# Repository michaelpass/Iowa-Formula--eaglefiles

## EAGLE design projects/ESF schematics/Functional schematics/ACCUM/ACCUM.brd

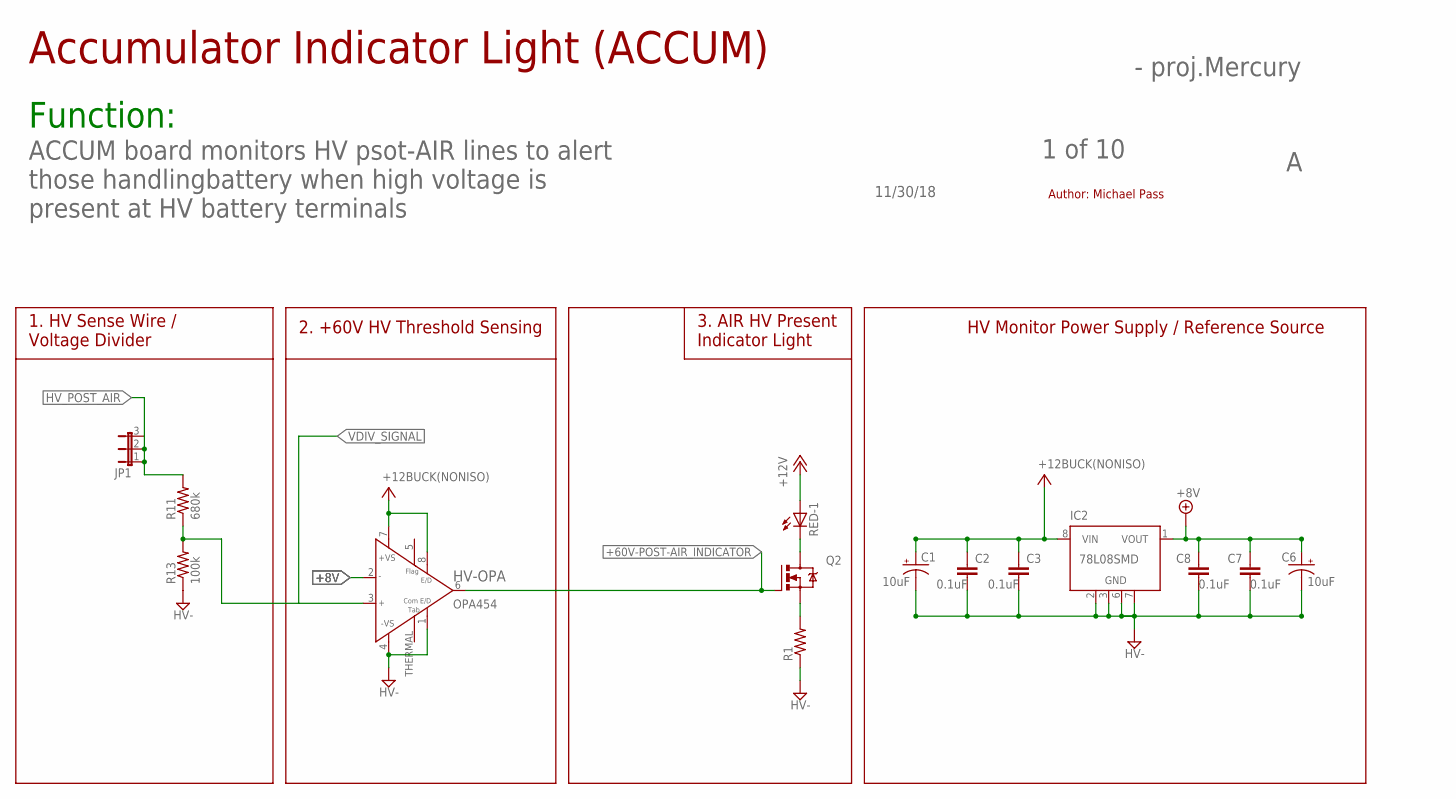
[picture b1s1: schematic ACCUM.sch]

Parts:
C1, C6: 10uF; 085CS_1AW
C2, C3, C7, C8: 0.1uF; C0805
HV-OPA: OPA454; SO08GP
IC2: 78L08SMD; SO08
JP1: JP2W
Q2: IRLZ44Z; TO220BH
R1: R-US_R0805; R0805
R11: 680k; R0805
R13: 100k; R0805
RED: LZR184

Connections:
+8V: C6.+, C7.1, C8.1, HV-OPA.2 (IN-), IC2.1 (VOUT)
+12V: RED.A1 (A)
+60V-POST-AIR_INDICATOR: HV-OPA.6 (OUT), Q2.G
GND: R1.1, R13.1
HV-: C1.-, C2.2, C3.2, C6.-, C7.2, C8.2, HV-OPA.1 (E/DCOM), HV-OPA.4 (-VS), IC2.2 (GND), IC2.3 (GND), IC2.6 (GND), IC2.7 (GND)
HV_POST_AIR: JP1.1, JP1.2, JP1.3, R11.2
unnamed: Q2.D, RED.K1 (C)
unnamed: Q2.S, R1.2
V+: C1.+, C2.1, C3.1, HV-OPA.7 (+VS), HV-OPA.8 (E/D), IC2.8 (VIN)
VDIV_SIGNAL: HV-OPA.3 (IN+), R11.1, R13.2

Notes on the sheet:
2. +60V HV Threshold Sensing
1. HV Sense Wire / Voltage Divider
HV Monitor Power Supply / Reference Source
3. AIR HV Present Indicator Light
Accumulator Indicator Light (ACCUM)
Function:
11/30/18
1 of 10
- proj.Mercury
ACCUM board monitors HV psot-AIR lines to alert those handlingbattery when high voltage is present at HV battery terminals
Author: Michael Pass

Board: 2 copper layers, 14 parts (0 on the bottom side), 9 nets, no tracks yet.

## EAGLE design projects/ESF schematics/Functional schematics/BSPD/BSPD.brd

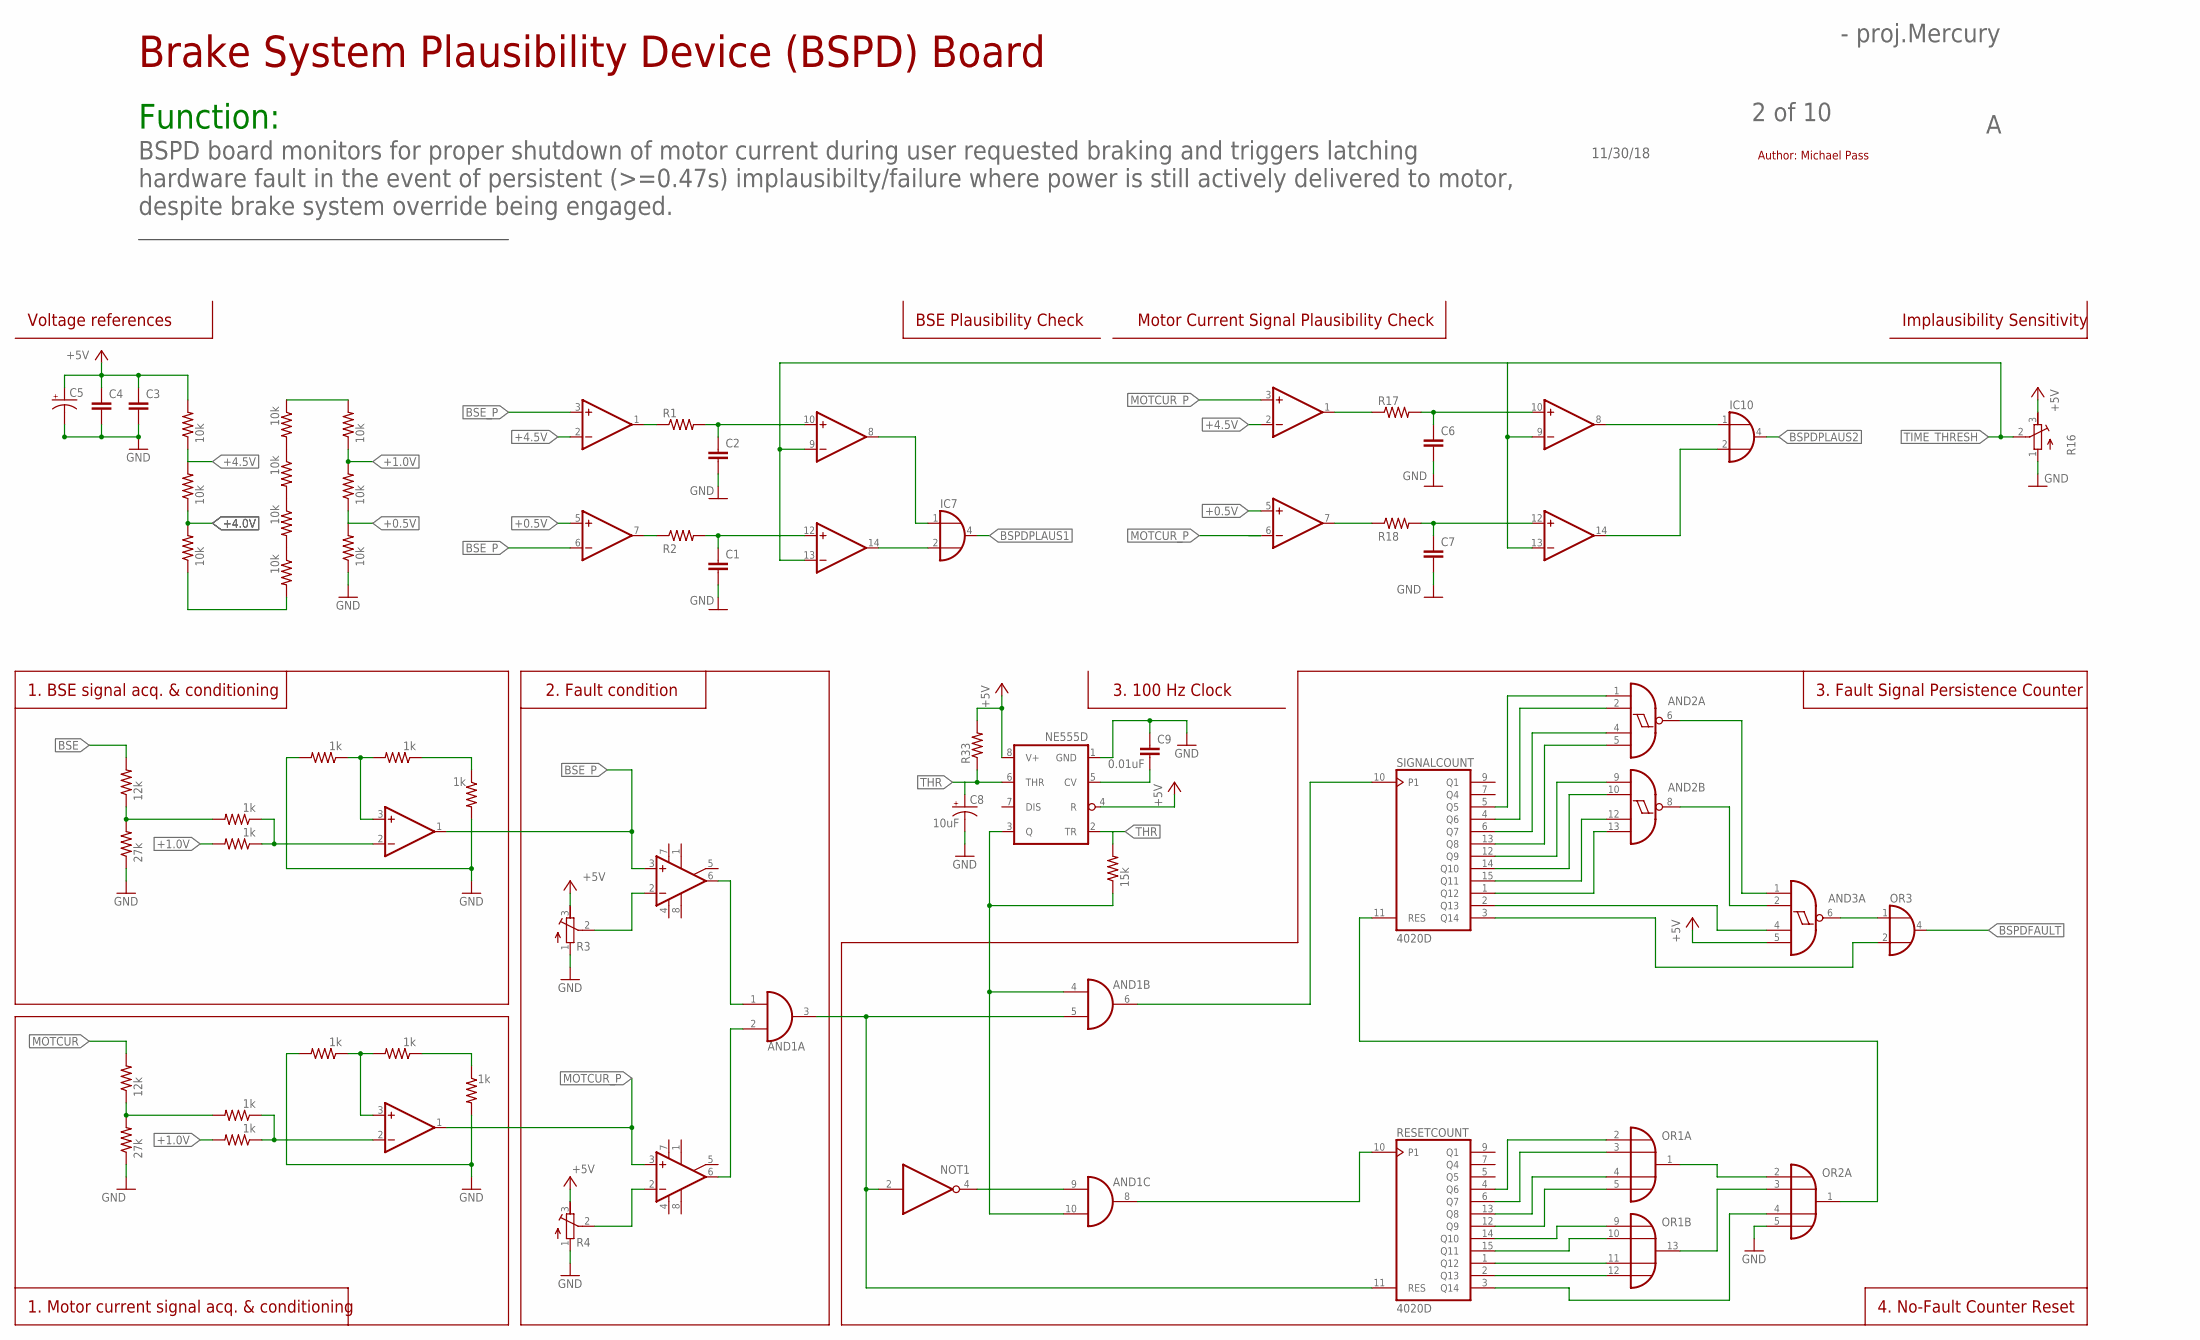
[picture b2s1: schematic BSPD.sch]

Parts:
AND1: 74ALS09D; SO14
AND2, AND3: 74HC13D; SO14
C1, C2, C3, C4, C6, C7: C-EUC0805; C0805
C5: CPOL-US085CS-1AR; 085CS_1AR
C8: 10uF; 085CS_1AW
C9: 0.01uF; C0805
IC1, IC2: LM741D; SO08
IC3, IC4, IC5, IC6: OP11D; SO14
IC7, IC10: 74AHC1G32DCK; SC70-5
IC9: NE555D; SO08
NOT1: 74AHC1G04DCK; SC70-5
OR1, OR2: 4072D; SO14
OR3: 74AHC1G32DCK; SC70-5
R1, R2, R17, R18, R33: R-US_R0805; R0805
R3, R4, R16: R-TRIMM3224X; RTRIM3224X
R5, R6, R8, R9, R10, R11, R12, R13, R14, R15: 10k; R0805
R7: 15k; R0805
R19, R21: 12k; R0805
R20, R22: 27k; R0805
R23, R24, R25, R26, R27, R28, R29, R30, R31, R32: 1k; R0805
RESETCOUNT: 4020D; SO16
SIGNALCOUNT: 4020D; SO16

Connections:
+0.5V: IC3.5 (+IN), IC5.5 (+IN), R14.1, R15.2
+1.0V: R13.1, R14.2, R24.2, R29.2
+4.0V: R6.1, R8.2
+4.5V: IC3.2 (-IN), IC5.2 (-IN), R5.1, R6.2
+5V: AND3.5 (I3), C3.1, C4.1, C5.+, IC9.4 (R), IC9.8 (V+), R3.3 (E), R4.3 (E), R5.2, R16.3 (E), R33.2
BSE: R19.2
BSE_P: IC1.3 (+IN), IC3.3 (+IN), IC3.6 (-IN), IC4.1 (OUT)
BSPDFAULT: OR3.4 (O)
BSPDPLAUS1: IC7.4 (O)
BSPDPLAUS2: IC10.4 (O)
GND: AND1.7 (GND), AND2.7 (GND), AND3.7 (GND), C1.2, C2.2, C3.2, C4.2, C5.-, C6.2, C7.2, C8.-, C9.1, IC7.3 (GND), IC9.1 (GND), IC10.3 (GND), NOT1.3 (GND), OR2.5 (I3), OR3.3 (GND), R3.1 (A), R4.1 (A), R15.1, R16.1 (A), R20.1, R22.1, R25.2, R27.2, R30.2, R32.2
MOTCUR: R21.2
MOTCUR_P: IC2.3 (+IN), IC5.3 (+IN), IC5.6 (-IN), IC6.1 (OUT)
unnamed: IC3.1 (OUT), R1.1
unnamed: R8.1, R9.2
unnamed: IC4.3 (+IN), R25.1, R26.2
unnamed: R9.1, R10.2
unnamed: R11.1, R12.2
unnamed: IC5.1 (OUT), R17.1
unnamed: R12.1, R13.2
unnamed: IC3.7 (OUT), R2.1
unnamed: R10.1, R11.2
unnamed: C2.1, IC3.10 (+IN), R1.2
unnamed: C1.1, IC3.12 (+IN), R2.2
unnamed: C6.1, IC5.10 (+IN), R17.2
unnamed: C7.1, IC5.12 (+IN), R18.2
unnamed: IC5.7 (OUT), R18.1
unnamed: IC6.3 (+IN), R30.1, R31.2
unnamed: R21.1, R22.2, R28.2
unnamed: R31.1, R32.1
unnamed: IC6.2 (-IN), R28.1, R29.1
unnamed: IC1.2 (-IN), R3.2 (S)
unnamed: R19.1, R20.2, R23.2
unnamed: IC2.2 (-IN), R4.2 (S)
unnamed: AND1.4 (I0), AND1.10 (I1), IC9.3 (Q), R7.1
unnamed: R26.1, R27.1
unnamed: IC4.2 (-IN), R23.1, R24.1
unnamed: C9.2, IC9.5 (CV)
unnamed: AND1.2 (I1), IC2.6 (OUT)
unnamed: AND1.1 (I0), IC1.6 (OUT)
unnamed: AND1.3 (O), AND1.5 (I1), NOT1.2 (I), RESETCOUNT.11 (RES)
unnamed: AND1.9 (I0), NOT1.4 (O)
unnamed: AND1.8 (O), RESETCOUNT.10 (P1)
unnamed: OR1.2 (I0), RESETCOUNT.4 (Q6)
unnamed: OR1.3 (I1), RESETCOUNT.6 (Q7)
unnamed: OR1.4 (I2), RESETCOUNT.13 (Q8)
unnamed: OR1.5 (I3), RESETCOUNT.12 (Q9)
unnamed: OR1.9 (I0), RESETCOUNT.14 (Q10)
unnamed: OR1.10 (I1), RESETCOUNT.15 (Q11)
unnamed: OR1.11 (I2), RESETCOUNT.1 (Q12)
unnamed: OR1.12 (I3), RESETCOUNT.2 (Q13)
unnamed: OR1.1 (O), OR2.2 (I0)
unnamed: OR1.13 (O), OR2.3 (I1)
unnamed: OR2.4 (I2), RESETCOUNT.3 (Q14)
unnamed: OR2.1 (O), SIGNALCOUNT.11 (RES)
unnamed: AND1.6 (O), SIGNALCOUNT.10 (P1)
unnamed: IC3.8 (OUT), IC7.1 (I0)
unnamed: IC3.14 (OUT), IC7.2 (I1)
unnamed: IC5.8 (OUT), IC10.1 (I0)
unnamed: IC5.14 (OUT), IC10.2 (I1)
unnamed: AND2.6 (O), AND3.1 (I0)
unnamed: AND2.8 (O), AND3.2 (I1)
unnamed: AND2.13 (I3), SIGNALCOUNT.1 (Q12)
unnamed: AND2.12 (I2), SIGNALCOUNT.15 (Q11)
unnamed: AND2.10 (I1), SIGNALCOUNT.14 (Q10)
unnamed: AND2.9 (I0), SIGNALCOUNT.12 (Q9)
unnamed: AND2.5 (I3), SIGNALCOUNT.13 (Q8)
unnamed: AND2.4 (I2), SIGNALCOUNT.6 (Q7)
unnamed: AND2.2 (I1), SIGNALCOUNT.4 (Q6)
unnamed: AND2.1 (I0), SIGNALCOUNT.5 (Q5)
unnamed: AND3.4 (I2), SIGNALCOUNT.2 (Q13)
unnamed: OR3.2 (I1), SIGNALCOUNT.3 (Q14)
unnamed: AND3.6 (O), OR3.1 (I0)
THR: C8.+, IC9.2 (TR), IC9.6 (THR), R7.2, R33.1
TIME_THRESH: IC3.9 (-IN), IC3.13 (-IN), IC5.9 (-IN), IC5.13 (-IN), R16.2 (S)
V+: IC1.7 (V+), IC2.7 (V+), IC3.4 (V+), IC4.4 (V+), IC5.4 (V+), IC6.4 (V+)
V-: IC1.4 (V-), IC2.4 (V-), IC3.11 (V-), IC4.11 (V-), IC5.11 (V-), IC6.11 (V-)
VCC: AND1.14 (VCC), AND2.14 (VCC), AND3.14 (VCC), IC7.5 (VCC), IC10.5 (VCC), NOT1.5 (VCC), OR3.5 (VCC)
VDD: OR1.14 (VDD), OR2.14 (VDD), RESETCOUNT.16 (VDD), SIGNALCOUNT.16 (VDD)
VSS: OR1.7 (VSS), OR2.7 (VSS), RESETCOUNT.8 (VSS), SIGNALCOUNT.8 (VSS)

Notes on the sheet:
Brake System Plausibility Device (BSPD) Board
Function:
11/30/18
2 of 10
- proj.Mercury
BSPD board monitors for proper shutdown of motor current during user requested braking and triggers latching hardware fault in the event of persistent (>=0.47s) implausibilty/failure where power is still actively delivered to motor, despite brake system override being engaged.
Voltage references
BSE Plausibility Check
Motor Current Signal Plausibility Check
1. BSE signal acq. & conditioning
3. 100 Hz Clock
3. Fault Signal Persistence Counter
Implausibility Sensitivity
4. No-Fault Counter Reset
2. Fault condition
1. Motor current signal acq. & conditioning
Author: Michael Pass

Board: 2 copper layers, 60 parts (0 on the bottom side), 75 nets, no tracks yet.

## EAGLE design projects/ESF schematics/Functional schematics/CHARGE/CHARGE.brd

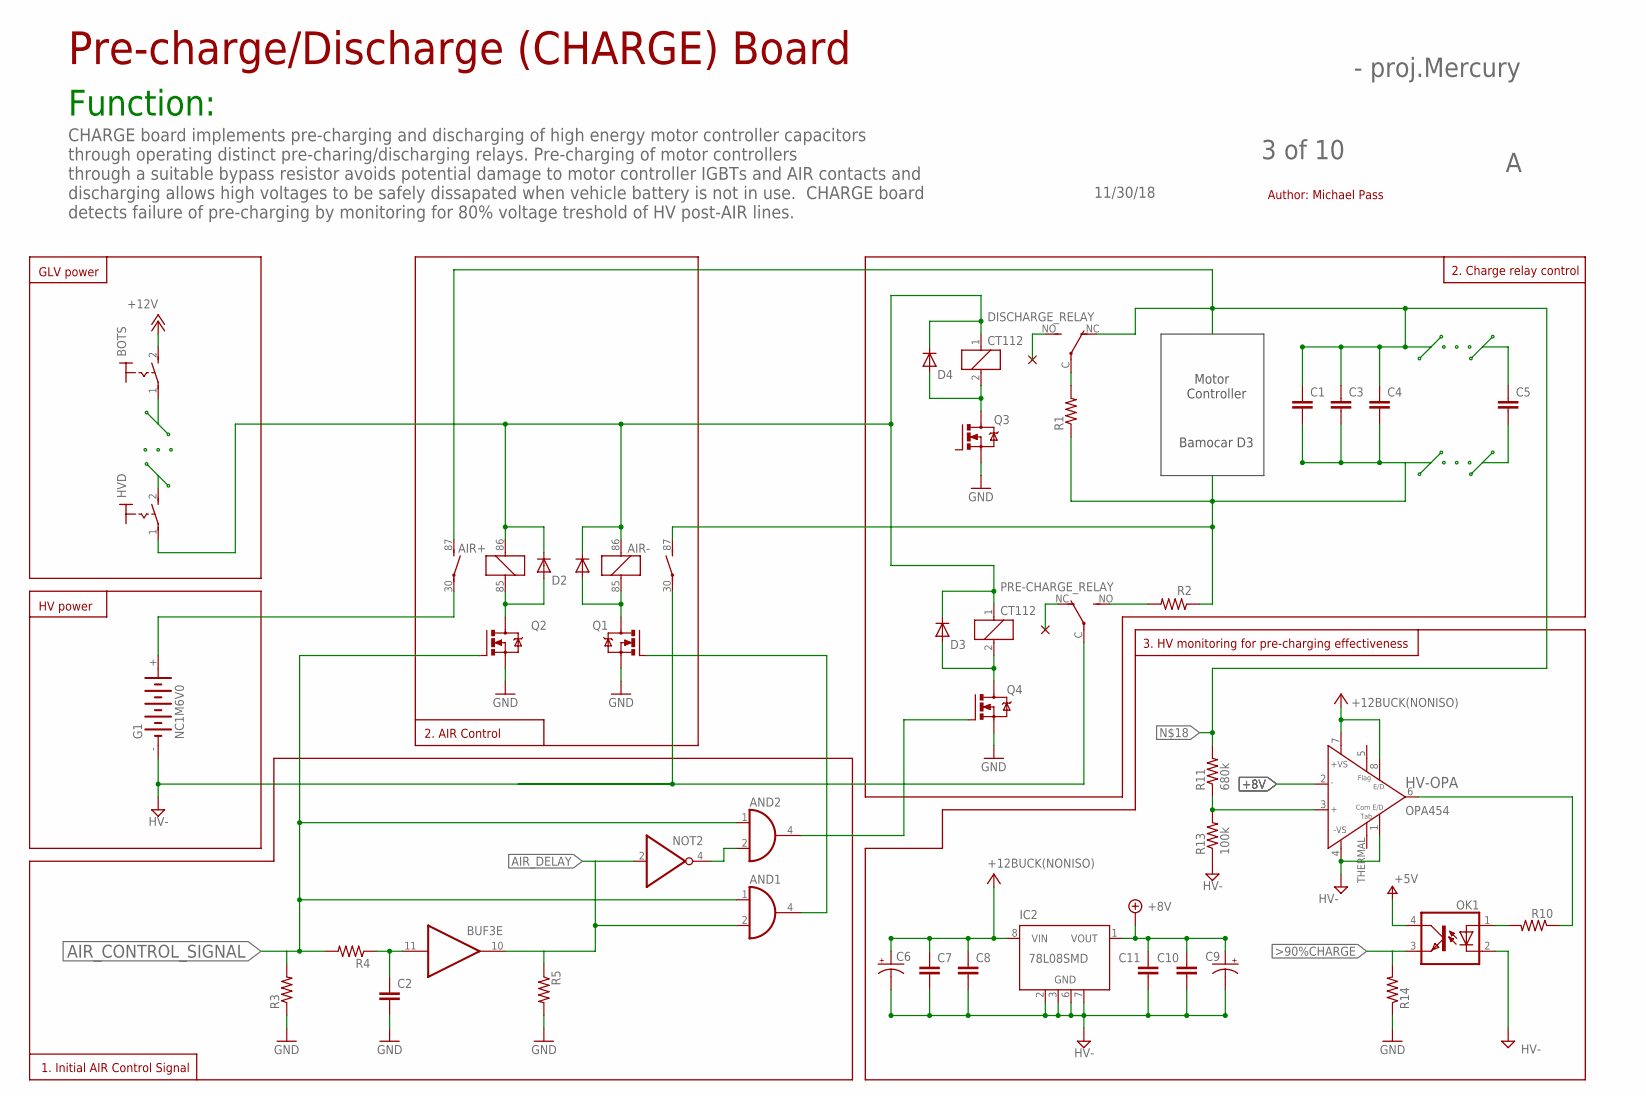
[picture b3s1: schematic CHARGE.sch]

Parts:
AIR+: CB1A-P-12V; CB1
AIR-: CB1A-P-12V; CB1
AND1, AND2: 74AHCT1G08DCK; SC70-5
BOTS: MS243
BUF3: 7407D; SO14
C1, C3, C4, C5: C-EU025-060X050; C025-060X050
C2: C-EUC0805; C0805
C6, C9: 10uF; 085CS_1AW
C7, C8, C10, C11: 0.1uF; C0805
D1, D2, D3, D4: 1N4933; DO41-10
DISCHARGE_RELAY: CT112; CT-SLIM
G1: NC1M6V0; NC1M
HV-OPA: OPA454; SO08GP
HVD: MS243
IC2: 78L08SMD; SO08
NOT2: 74LVC1G06DCK; SC70-5
OK1: PC817-S; SOP04(2.54)
PRE-CHARGE_RELAY: CT112; CT-SLIM
Q1, Q2, Q3, Q4: IRLZ44Z; TO220BH
R1, R2: R-US_0309/12; 0309/12
R3, R4, R5, R10, R14: R-US_R0805; R0805
R11: 680k; R0805
R13: 100k; R0805

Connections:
+8V: C9.+, C10.1, C11.1, HV-OPA.2 (IN-), IC2.1 (VOUT)
+12V: BOTS.2 (S)
>90%CHARGE: OK1.3 (EMIT), R14.2
AIR_CONTROL_SIGNAL: AND1.1 (I0), AND2.1 (I0), Q2.G, R3.2, R4.2
AIR_DELAY: AND1.2 (I1), BUF3.10 (O), NOT2.2 (I), R5.1
GND: AIR-.30, AND1.3 (GND), AND2.3 (GND), BUF3.7 (GND), C2.2, G1.-, NOT2.3 (GND), OK1.2 (C), PRE-CHARGE_RELAY.C, Q1.S, Q2.S, Q3.S, Q4.S, R3.1, R5.2, R13.1, R14.1
HV+: AIR+.30, G1.+
HV-: C6.-, C7.2, C8.2, C9.-, C10.2, C11.2, HV-OPA.1 (E/DCOM), HV-OPA.4 (-VS), IC2.2 (GND), IC2.3 (GND), IC2.6 (GND), IC2.7 (GND)
HV-_CONTROL: AND1.4 (O), Q1.G
unnamed: PRE-CHARGE_RELAY.NO (S), R2.2
unnamed: AND2.4 (O), Q4.G
unnamed: D3.A, PRE-CHARGE_RELAY.2, Q4.D
unnamed: AIR+.85 (2), D2.A, Q2.D
unnamed: HV-OPA.6 (OUT), R10.1
unnamed: AIR-.85 (2), D1.A, Q1.D
unnamed: D4.A, DISCHARGE_RELAY.2, Q3.D
unnamed: AIR+.86 (1), AIR-.86 (1), D1.C, D2.C, D3.C, D4.C, DISCHARGE_RELAY.1, HVD.1, PRE-CHARGE_RELAY.1
unnamed: DISCHARGE_RELAY.C, R1.2
unnamed: OK1.1 (A), R10.2
unnamed: AIR+.87 (S), C1.1, C3.1, C4.1, DISCHARGE_RELAY.NC (O), R11.2
unnamed: BUF3.11 (I), C2.1, R4.1
unnamed: AND2.2 (I1), NOT2.4 (O)
unnamed: AIR-.87 (S), C1.2, C3.2, C4.2, R1.1, R2.1
V+: C6.+, C7.1, C8.1, HV-OPA.7 (+VS), HV-OPA.8 (E/D), IC2.8 (VIN), OK1.4 (COL)
VCC: AND1.5 (VCC), AND2.5 (VCC), BUF3.14 (VCC), NOT2.5 (VCC)
VDIV_SIGNAL: HV-OPA.3 (IN+), R11.1, R13.2

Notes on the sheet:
Bamocar D3
Motor Controller
11/30/18
3 of 10
- proj.Mercury
Author: Michael Pass
Function:
CHARGE board implements pre-charging and discharging of high energy motor controller capacitors through operating distinct pre-charing/discharging relays. Pre-charging of motor controllers through a suitable bypass resistor avoids potential damage to motor controller IGBTs and AIR contacts and disc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
Pre-charge/Discharge (CHARGE) Board
GLV power
HV power
1. Initial AIR Control Signal
2. AIR Control
2. Charge relay control
3. HV monitoring for pre-charging effectiveness

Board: 2 copper layers, 42 parts (0 on the bottom side), 25 nets, no tracks yet.

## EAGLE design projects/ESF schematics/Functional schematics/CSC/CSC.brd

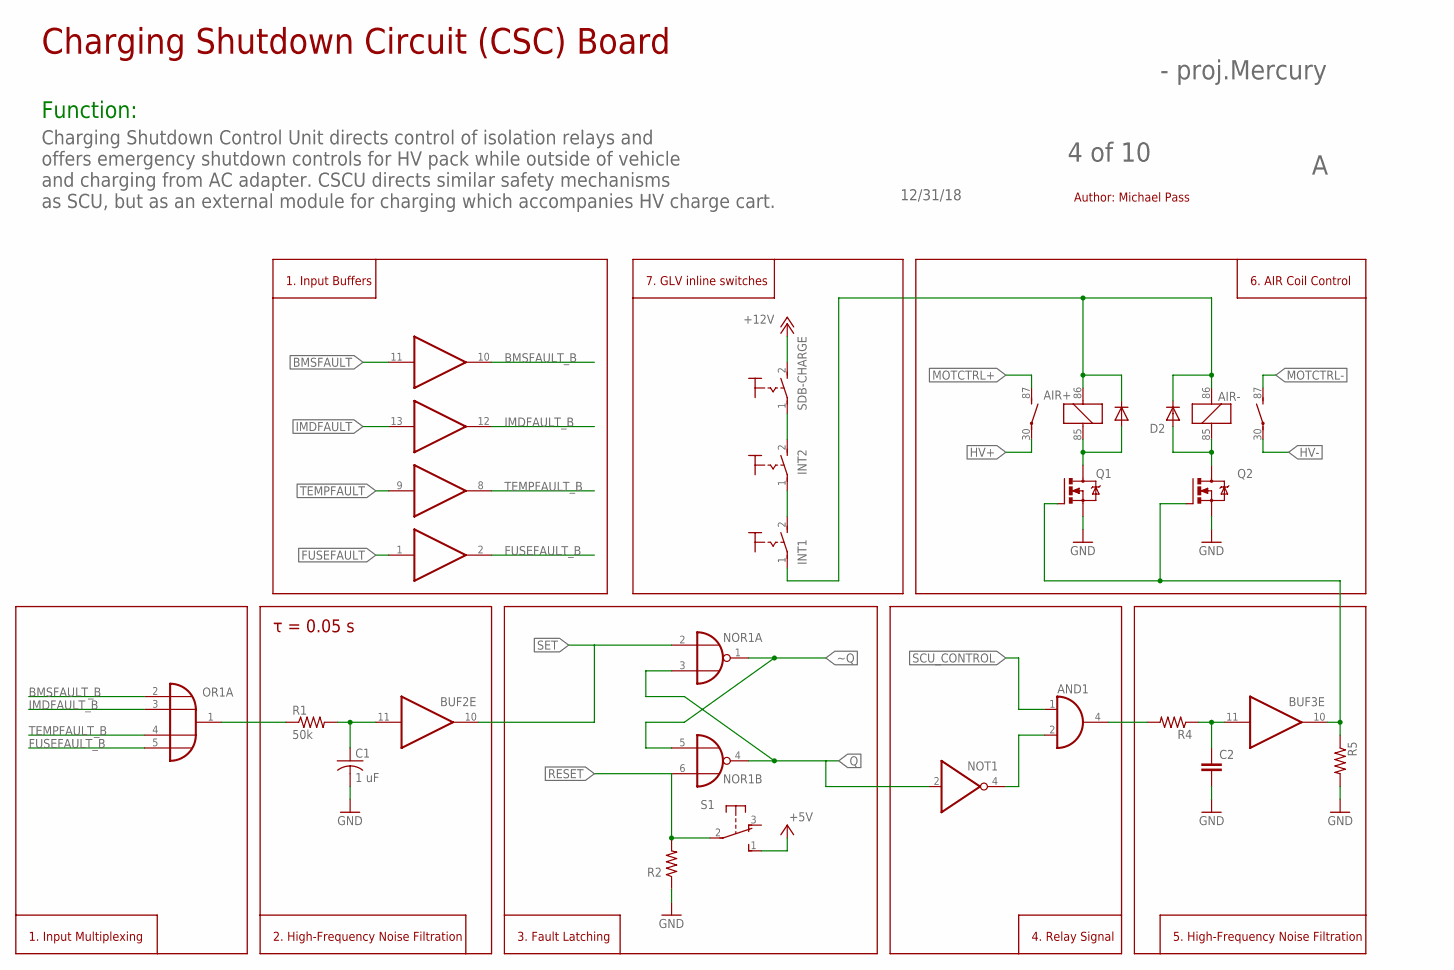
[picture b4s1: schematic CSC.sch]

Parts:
AIR+: CB1A-P-12V; CB1
AIR-: CB1A-P-12V; CB1
AND1: 74AHCT1G08DCK; SC70-5
BUF1, BUF2, BUF3: 7407D; SO14
C1: 1 uF; C0805
C2: C-EUC0805; C0805
D1, D2: 1N4933; DO41-10
INT1, INT2: MS243
NOR1: 74LS33D; SO14
NOT1: 74LVC1G06DCK; SC70-5
OR1: 4072D; SO14
Q1, Q2: IRLZ44Z; TO220BH
R1: 50k; R0805
R2, R4, R5: R-US_R0805; R0805
S1: 9077-1
SDB-CHARGE: MS243

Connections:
+5V: S1.1 (S)
+12V: SDB-CHARGE.2 (S)
AIR_CONTROL_SIGNAL: BUF3.10 (O), Q1.G, Q2.G, R5.1
BMSFAULT: BUF1.11 (I)
BMSFAULT_B: BUF1.10 (O), OR1.2 (I0)
FUSEFAULT: BUF2.1 (I)
FUSEFAULT_B: BUF2.2 (O), OR1.5 (I3)
GND: AND1.3 (GND), BUF1.7 (GND), BUF2.7 (GND), BUF3.7 (GND), C1.2, C2.2, NOR1.7 (GND), NOT1.3 (GND), Q1.S, Q2.S, R2.1, R5.2
HV+: AIR+.30
HV-: AIR-.30
IMDFAULT: BUF1.13 (I)
IMDFAULT_B: BUF1.12 (O), OR1.3 (I1)
MOTCTRL+: AIR+.87 (S)
MOTCTRL-: AIR-.87 (S)
unnamed: AND1.4 (O), R4.2
unnamed: AIR+.86 (1), AIR-.86 (1), D1.C, D2.C, INT1.1
unnamed: OR1.1 (O), R1.1
unnamed: BUF2.11 (I), C1.1, R1.2
unnamed: AIR-.85 (2), D2.A, Q2.D
unnamed: AND1.2 (I1), NOT1.4 (O)
unnamed: AIR+.85 (2), D1.A, Q1.D
unnamed: INT2.2 (S), SDB-CHARGE.1
unnamed: INT1.2 (S), INT2.1
unnamed: BUF3.11 (I), C2.1, R4.1
Q: NOR1.3 (I1), NOR1.4 (O), NOT1.2 (I)
RESET: NOR1.6 (I1), R2.2, S1.2
SCU_CONTROL: AND1.1 (I0)
SET: BUF2.10 (O), NOR1.2 (I0)
TEMPFAULT: BUF1.9 (I)
TEMPFAULT_B: BUF1.8 (O), OR1.4 (I2)
VCC: AND1.5 (VCC), BUF1.14 (VCC), BUF2.14 (VCC), BUF3.14 (VCC), NOR1.14 (VCC), NOT1.5 (VCC)
VDD: OR1.14 (VDD)
VSS: OR1.7 (VSS)
~Q: NOR1.1 (O), NOR1.5 (I0)

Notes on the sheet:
1. Input Multiplexing
2. High-Frequency Noise Filtration
4. Relay Signal
3. Fault Latching
1. Input Buffers
τ = 0.05 s
6. AIR Coil Control
7. GLV inline switches
12/31/18
4 of 10
- proj.Mercury
Charging Shutdown Circuit (CSC) Board
Function:
Charging Shutdown Control Unit directs control of isolation relays and offers emergency shutdown controls for HV pack while outside of vehicle and charging from AC adapter. CSCU directs similar safety mechanisms as SCU, but as an external module for charging which accompanies HV charge cart.
5. High-Frequency Noise Filtration
Author: Michael Pass

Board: 2 copper layers, 23 parts (0 on the bottom side), 21 nets, no tracks yet.

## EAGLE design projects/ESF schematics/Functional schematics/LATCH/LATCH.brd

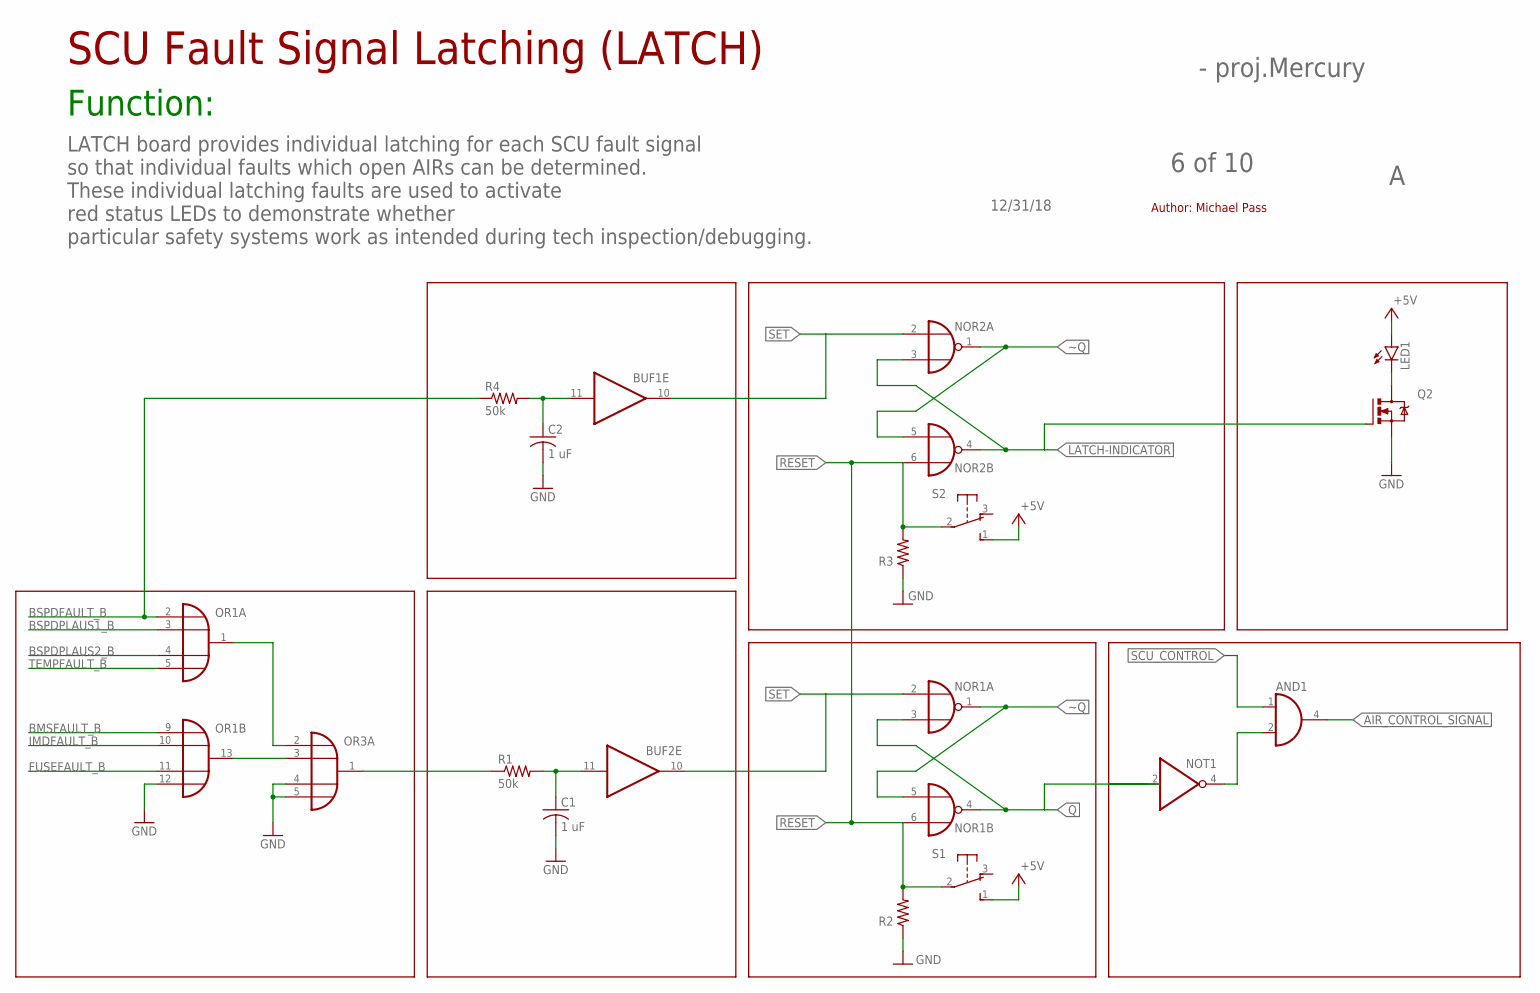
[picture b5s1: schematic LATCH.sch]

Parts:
AND1: 74AHCT1G08DCK; SC70-5
BUF1, BUF2: 7407D; SO14
C1, C2: 1 uF; C0805
LED1: LED10MM
NOR1, NOR2: 74LS33D; SO14
NOT1: 74LVC1G06DCK; SC70-5
OR1, OR3: 4072D; SO14
Q2: IRLZ44Z; TO220BH
R1, R4: 50k; R0805
R2, R3: R-US_R0805; R0805
S1, S2: 9077-1

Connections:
+5V: LED1.A, S1.1 (S), S2.1 (S)
AIR_CONTROL_SIGNAL: AND1.4 (O)
BMSFAULT_B: OR1.9 (I0)
BSPDFAULT_B: OR1.2 (I0), R4.1
BSPDPLAUS1_B: OR1.3 (I1)
BSPDPLAUS2_B: OR1.4 (I2)
FUSEFAULT_B: OR1.11 (I2)
GND: C1.2, C2.2, OR1.12 (I3), Q2.S, R2.1, R3.1
IMDFAULT_B: OR1.10 (I1)
LATCH-INDICATOR: NOR2.3 (I1), NOR2.4 (O), Q2.G
unnamed: OR1.1 (O), OR3.2 (I0)
unnamed: OR1.13 (O), OR3.3 (I1)
unnamed: AND1.3 (GND), BUF1.7 (GND), BUF2.7 (GND), NOR1.7 (GND), NOR2.7 (GND), NOT1.3 (GND), OR3.4 (I2), OR3.5 (I3)
unnamed: LED1.K (C), Q2.D
unnamed: OR3.1 (O), R1.1
unnamed: BUF2.11 (I), C1.1, R1.2
unnamed: BUF1.11 (I), C2.1, R4.2
unnamed: AND1.2 (I1), NOT1.4 (O)
Q: NOR1.3 (I1), NOR1.4 (O), NOT1.2 (I)
RESET: NOR1.6 (I1), NOR2.6 (I1), R2.2, R3.2, S1.2, S2.2
SCU_CONTROL: AND1.1 (I0)
SET: BUF1.10 (O), BUF2.10 (O), NOR1.2 (I0), NOR2.2 (I0)
TEMPFAULT_B: OR1.5 (I3)
VCC: AND1.5 (VCC), BUF1.14 (VCC), BUF2.14 (VCC), NOR1.14 (VCC), NOR2.14 (VCC), NOT1.5 (VCC)
VDD: OR1.14 (VDD), OR3.14 (VDD)
VSS: OR1.7 (VSS), OR3.7 (VSS)
~Q: NOR1.1 (O), NOR1.5 (I0), NOR2.1 (O), NOR2.5 (I0)

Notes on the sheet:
12/31/18
6 of 10
- proj.Mercury
SCU Fault Signal Latching (LATCH)
Function:
LATCH board provides individual latching for each SCU fault signal so that individual faults which open AIRs can be determined. These individual latching faults are used to activate red status LEDs to demonstrate whether particular safety systems work as intended during tech inspection/debugging.
Author: Michael Pass

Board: 2 copper layers, 18 parts (0 on the bottom side), 19 nets, no tracks yet.

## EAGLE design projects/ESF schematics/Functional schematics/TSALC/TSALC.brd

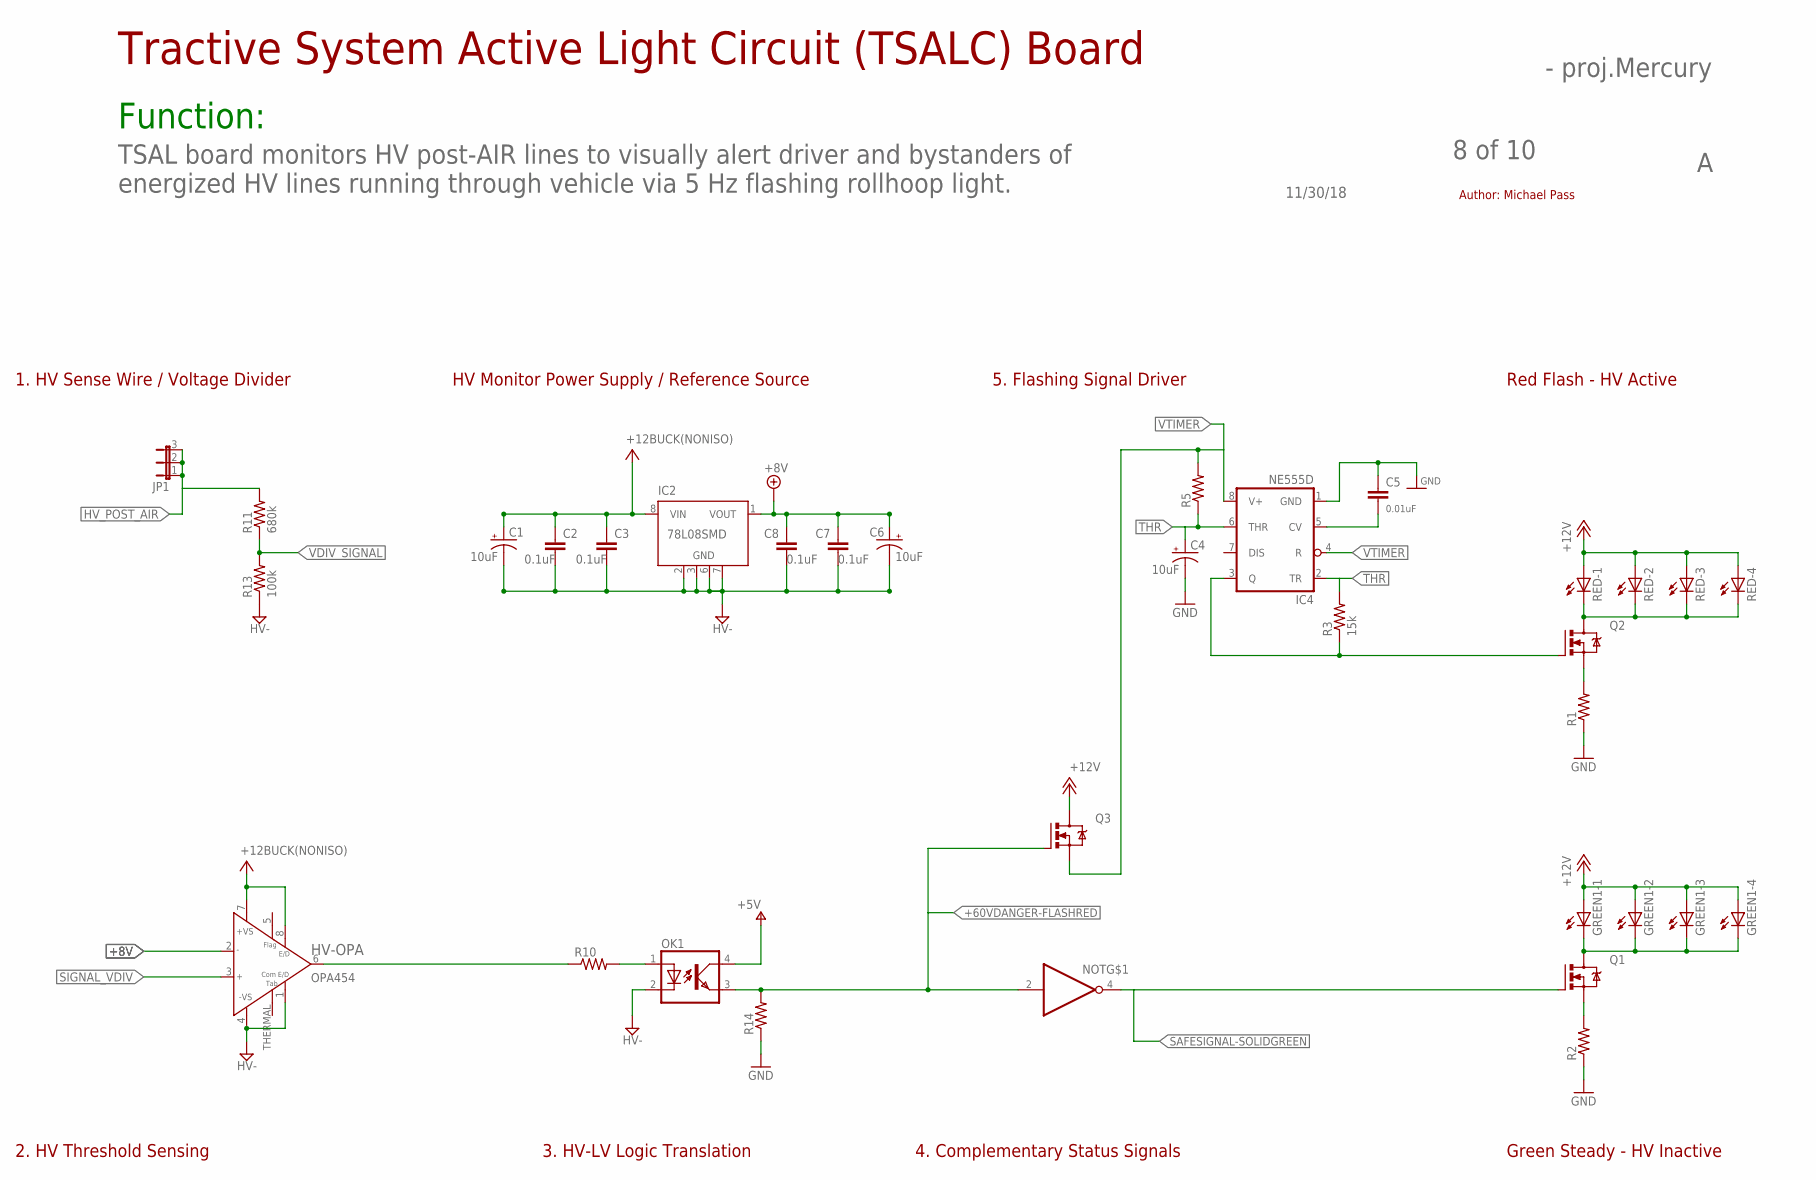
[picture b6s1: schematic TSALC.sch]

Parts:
C1, C4, C6: 10uF; 085CS_1AW
C2, C3, C7, C8: 0.1uF; C0805
C5: 0.01uF; C0805
GREEN1: LZR184
HV-OPA: OPA454; SO08GP
IC2: 78L08SMD; SO08
IC4: NE555D; SO08
JP1: JP2W
NOT: 74LVC1G06DCK; SC70-5
OK1: PC817-S; SOP04(2.54)
Q1, Q2, Q3: IRLZ44Z; TO220BH
R1, R2, R5, R10, R14: R-US_R0805; R0805
R3: 15k; R0805
R11: 680k; R0805
R13: 100k; R0805
RED: LZR184

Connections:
+8V: C6.+, C7.1, C8.1, HV-OPA.2 (IN-), IC2.1 (VOUT)
+12V: GREEN1.A1 (A), GREEN1.A2 (A), GREEN1.A3 (A), GREEN1.A4 (A), Q3.D, RED.A1 (A), RED.A2 (A), RED.A3 (A), RED.A4 (A)
+60VDANGER-FLASHRED: NOT.2 (I), OK1.3 (EMIT), Q3.G, R14.2
GND: C4.-, C5.1, IC4.1 (GND), OK1.2 (C), R1.1, R2.1, R13.1, R14.1
HV-: C1.-, C2.2, C3.2, C6.-, C7.2, C8.2, HV-OPA.1 (E/DCOM), HV-OPA.4 (-VS), IC2.2 (GND), IC2.3 (GND), IC2.6 (GND), IC2.7 (GND), NOT.3 (GND)
HV_POST_AIR: JP1.1, JP1.2, JP1.3, R11.2
unnamed: GREEN1.K1 (C), GREEN1.K2 (C), GREEN1.K3 (C), GREEN1.K4 (C), Q1.D
unnamed: Q1.S, R2.2
unnamed: Q2.D, RED.K1 (C), RED.K2 (C), RED.K3 (C), RED.K4 (C)
unnamed: Q2.S, R1.2
unnamed: C5.2, IC4.5 (CV)
unnamed: IC4.3 (Q), Q2.G, R3.1
unnamed: HV-OPA.6 (OUT), R10.1
unnamed: OK1.1 (A), R10.2
SAFESIGNAL-SOLIDGREEN: NOT.4 (O), Q1.G
SIGNAL_VDIV: HV-OPA.3 (IN+)
THR: C4.+, IC4.2 (TR), IC4.6 (THR), R3.2, R5.1
V+: C1.+, C2.1, C3.1, HV-OPA.7 (+VS), HV-OPA.8 (E/D), IC2.8 (VIN), OK1.4 (COL)
VCC: NOT.5 (VCC)
VDIV_SIGNAL: R11.1, R13.2
VTIMER: IC4.4 (R), IC4.8 (V+), Q3.S, R5.2

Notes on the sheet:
2. HV Threshold Sensing
3. HV-LV Logic Translation
1. HV Sense Wire / Voltage Divider
4. Complementary Status Signals
HV Monitor Power Supply / Reference Source
5. Flashing Signal Driver
Red Flash - HV Active
Green Steady - HV Inactive
Tractive System Active Light Circuit (TSALC) Board
Function:
11/30/18
8 of 10
- proj.Mercury
TSAL board monitors HV post-AIR lines to visually alert driver and bystanders of energized HV lines running through vehicle via 5 Hz flashing rollhoop light.
Author: Michael Pass

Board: 2 copper layers, 27 parts (0 on the bottom side), 19 nets, no tracks yet.

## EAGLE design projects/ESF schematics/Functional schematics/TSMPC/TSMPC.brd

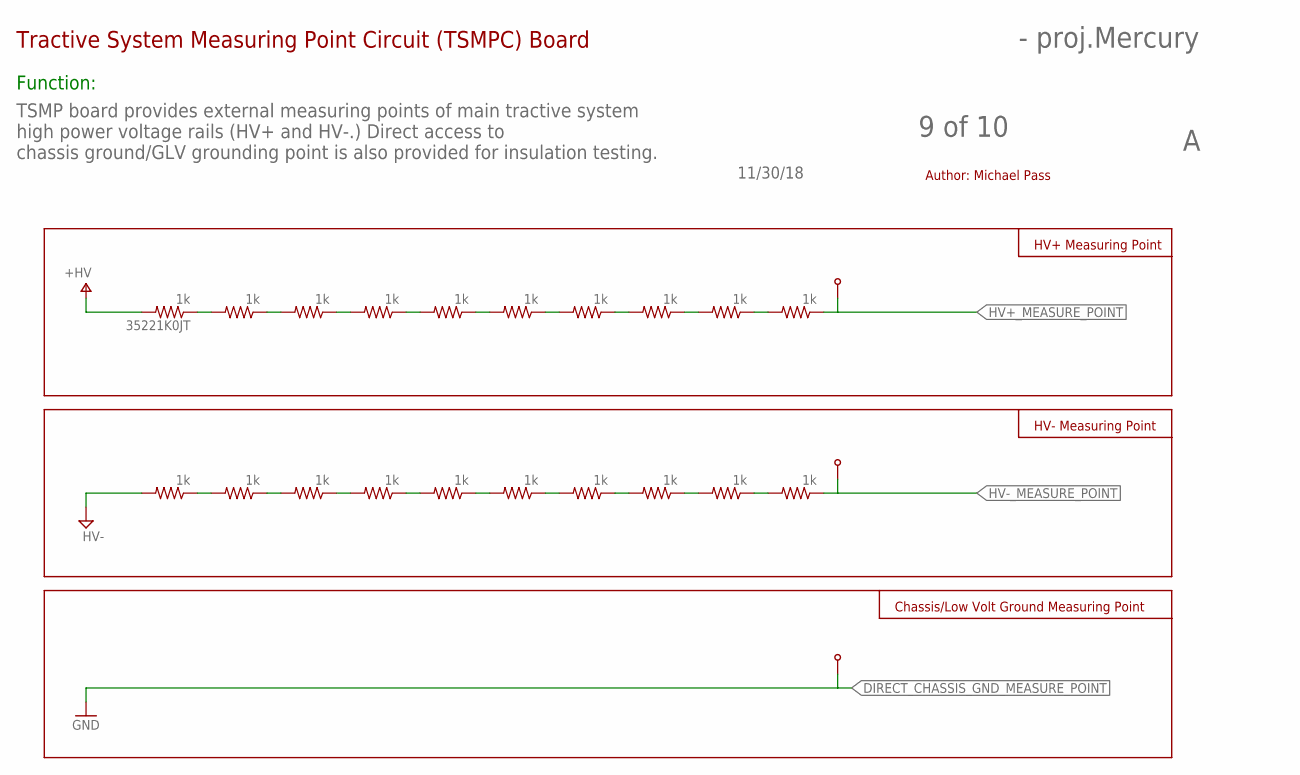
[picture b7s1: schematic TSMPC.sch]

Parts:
35221K0JT: 1k; R0805
R2, R3, R4, R5, R6, R7, R8, R9, R10, R21, R22, R23, R24, R25, R26, R27, R28, R29, R30: 1k; R0805
U$1, U$3, U$4: BANANA-JACK; BANANA-PRINT

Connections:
DIRECT_CHASSIS_GND_MEASURE_POINT: R21.2, U$3.P$1
HV+_MEASURE_POINT: R10.1, U$1.P$1
HV-_MEASURE_POINT: R30.1, U$4.P$1
unnamed: 35221K0JT.1, R2.2
unnamed: R2.1, R3.2
unnamed: R3.1, R4.2
unnamed: R4.1, R5.2
unnamed: R5.1, R6.2
unnamed: R6.1, R7.2
unnamed: R7.1, R8.2
unnamed: R8.1, R9.2
unnamed: R9.1, R10.2
unnamed: R21.1, R22.2
unnamed: R22.1, R23.2
unnamed: R23.1, R24.2
unnamed: R24.1, R25.2
unnamed: R25.1, R26.2
unnamed: R26.1, R27.2
unnamed: R27.1, R28.2
unnamed: R28.1, R29.2
unnamed: R29.1, R30.2
V+: 35221K0JT.2

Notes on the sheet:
Tractive System Measuring Point Circuit (TSMPC) Board
Function:
11/30/18
9 of 10
- proj.Mercury
TSMP board provides external measuring points of main tractive system high power voltage rails (HV+ and HV-.) Direct access to chassis ground/GLV grounding point is also provided for insulation testing.
Author: Michael Pass
HV+ Measuring Point
HV- Measuring Point
Chassis/Low Volt Ground Measuring Point

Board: 2 copper layers, 23 parts (0 on the bottom side), 21 nets, no tracks yet.
